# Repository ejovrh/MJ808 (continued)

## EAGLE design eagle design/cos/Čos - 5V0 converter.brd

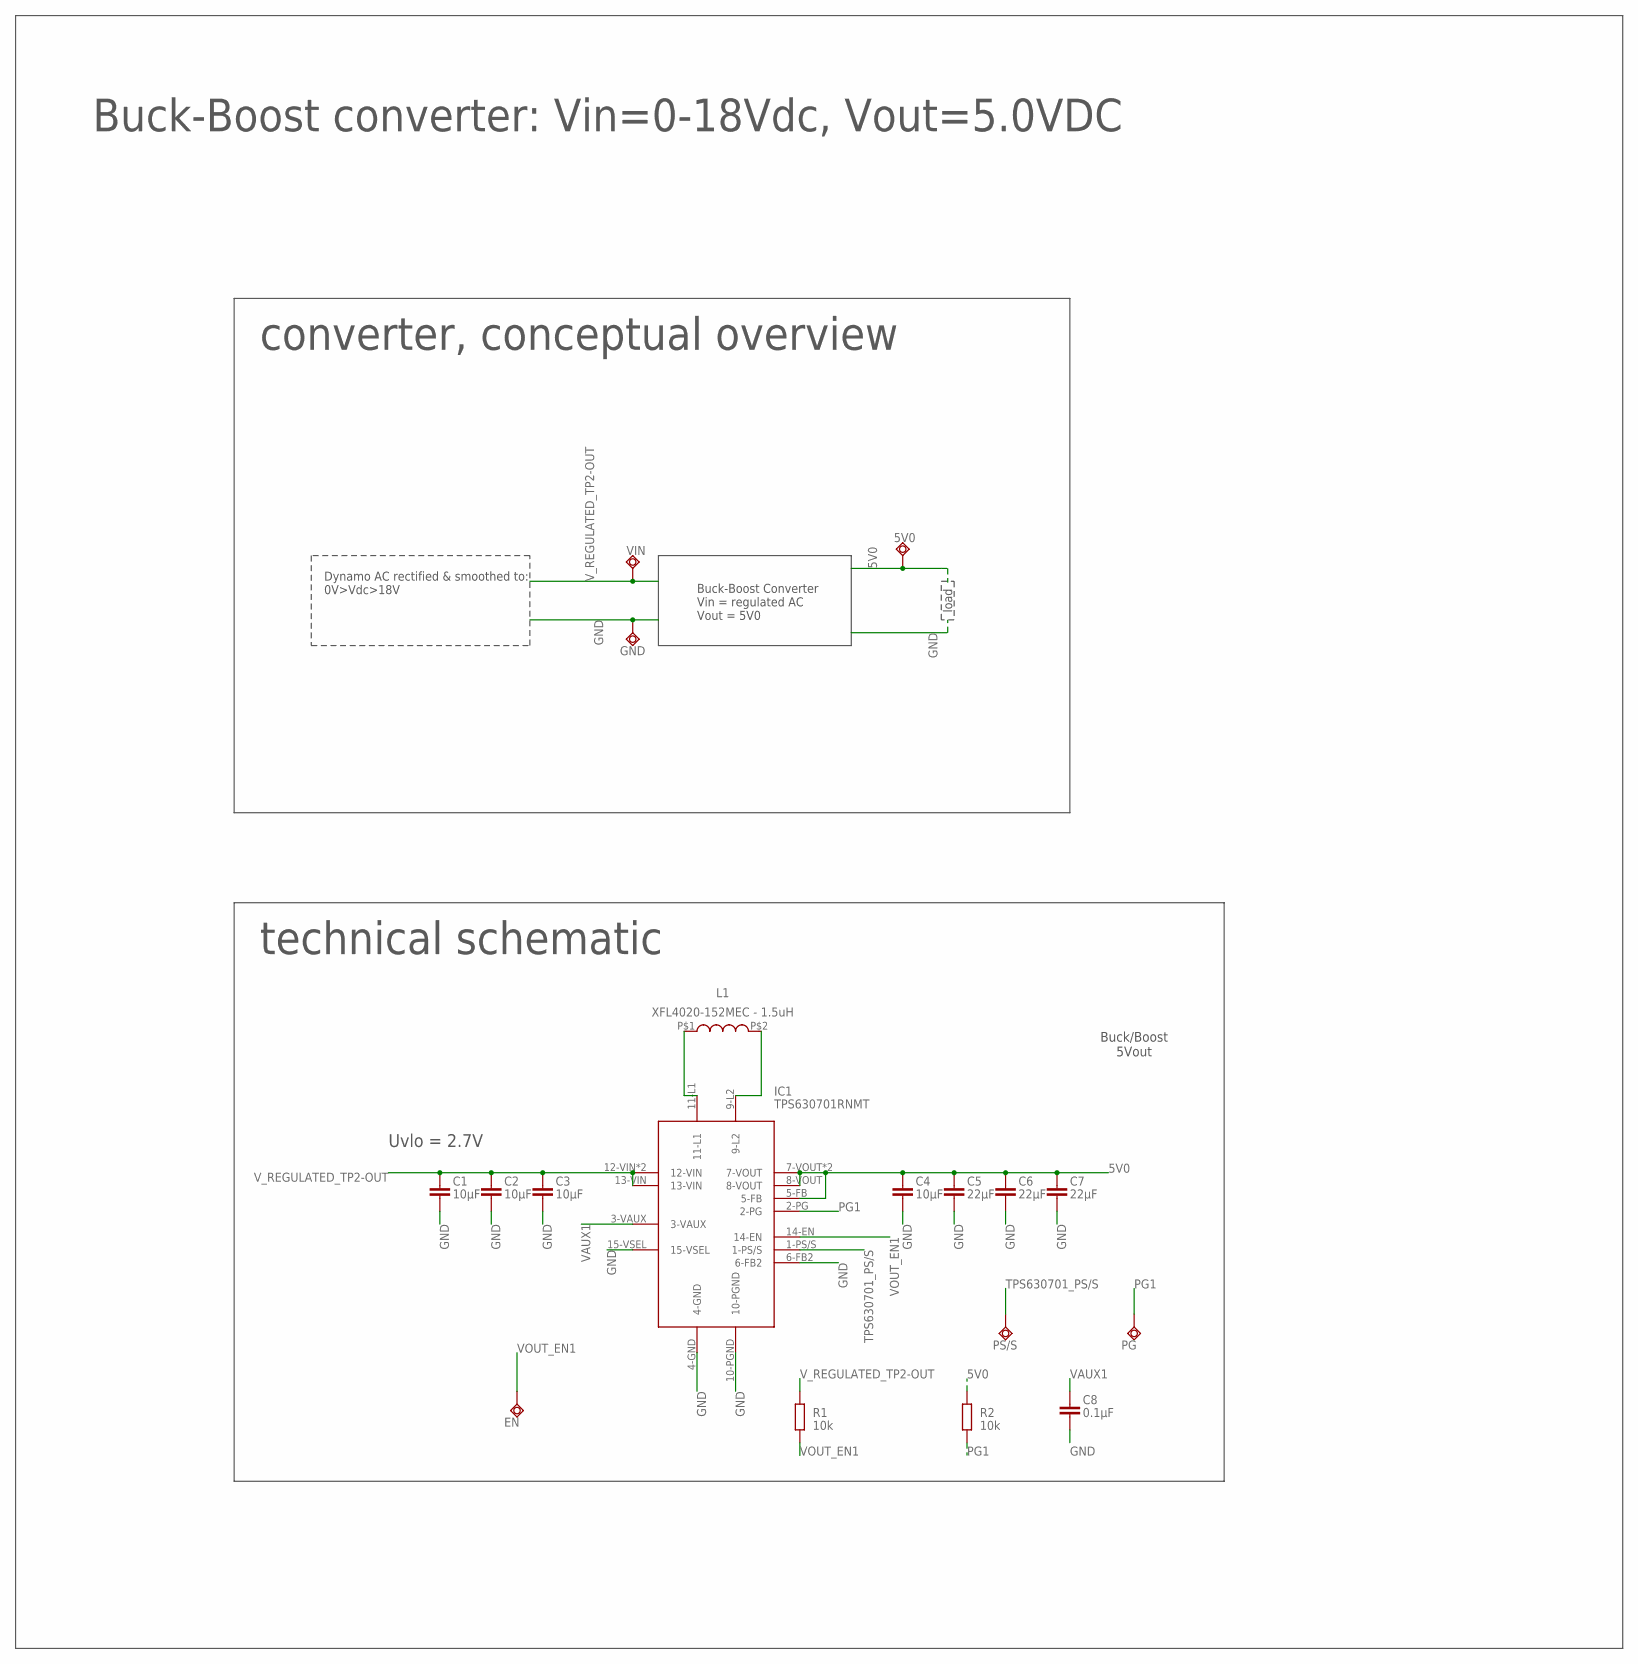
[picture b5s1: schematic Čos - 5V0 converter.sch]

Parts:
5V0: TPSQPAD1-13; P1-13
C1, C2: 10μF; C0805
C3, C4: 10μF; C0603
C5, C6, C7: 22μF; C0805
C8: 0.1μF; C0402
EN: TPSQTP13R; TP13R
GND: TPSQPAD1-13; P1-13
IC1: TPS630701RNMT; VQFN
L1: XFL4020-152MEC - 1.5uH; SMD
PG: TPSQTP13R; TP13R
PS/S: TPSQTP13R; TP13R
R1, R2: 10k; R0402
VIN: TPSQPAD1-13; P1-13

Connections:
5V0: 5V0.TP, C4.1, C5.1, C6.1, C7.1, IC1.5-FB, IC1.7-VOUT, IC1.8-VOUT, IC1.VOUT (7-VOUT), R2.2
GND: C1.2, C2.2, C3.2, C4.2, C5.2, C6.2, C7.2, C8.2, GND.TP, IC1.4-GND, IC1.6-FB2, IC1.10-PGND, IC1.15-VSEL
unnamed: IC1.11-L1, L1.P$1
unnamed: IC1.9-L2, L1.P$2
PG1: IC1.2-PG, PG.TP, R2.1
TPS630701_PS/S: IC1.1-PS/S, PS/S.TP
VAUX1: C8.1, IC1.3-VAUX
VOUT_EN1: EN.TP, IC1.14-EN, R1.1
V_REGULATED_TP2-OUT: C1.1, C2.1, C3.1, IC1.12-VIN, IC1.13-VIN, IC1.VIN (12-VIN), R1.2, VIN.TP

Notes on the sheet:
Buck-Boost converter: Vin=0-18Vdc, Vout=5.0VDC
technical schematic
converter, conceptual overview
Buck/Boost 5Vout
Uvlo = 2.7V
Buck-Boost Converter Vin = regulated AC Vout = 5V0
Dynamo AC rectified & smoothed to: 0V>Vdc>18V
load

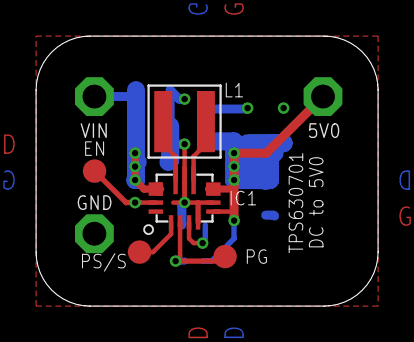
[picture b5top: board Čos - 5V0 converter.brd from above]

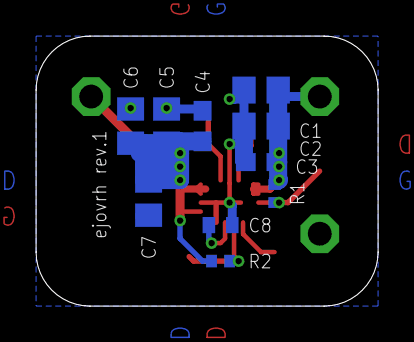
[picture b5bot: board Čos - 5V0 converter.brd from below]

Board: 2 copper layers, 19.0 x 15.0 mm, 18 parts (10 on the bottom side), 9 nets.

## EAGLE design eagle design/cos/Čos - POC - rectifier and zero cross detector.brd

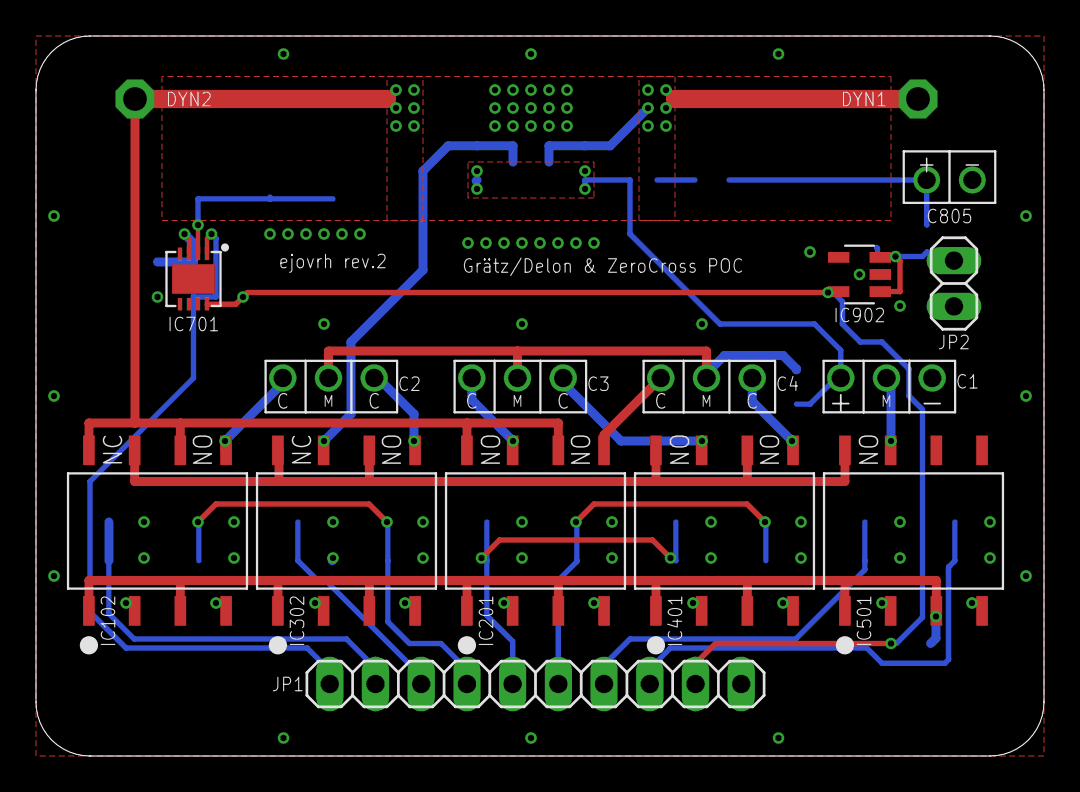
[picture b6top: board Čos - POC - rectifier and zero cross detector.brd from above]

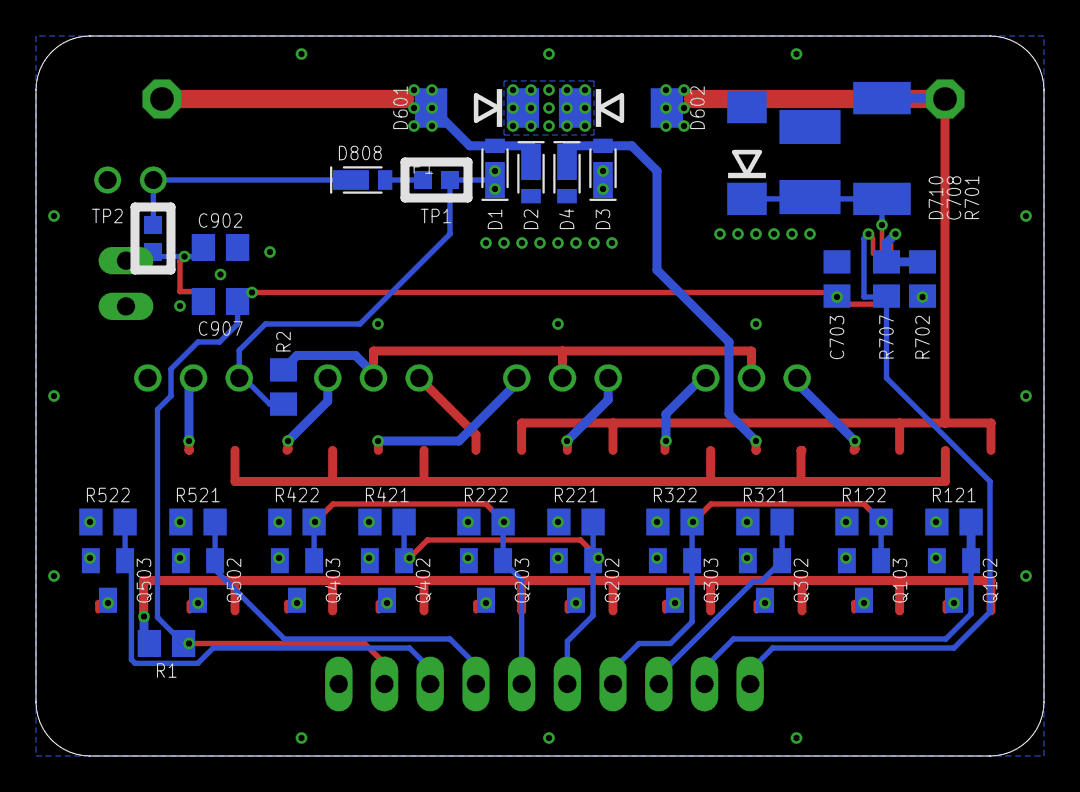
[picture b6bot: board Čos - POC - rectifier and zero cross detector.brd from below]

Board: 2 copper layers, 56.0 x 40.0 mm, 57 parts (41 on the bottom side), 40 nets.

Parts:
C1: 330μF / 35V / ultralow ESR; TH-2S
C2, C3, C4: 1500μF / 35V / ultralow ESR; TH-2S-BACK-TO-BACK
C703: 0.1uF / 10V; C0805
C708: 10nF / 100v; C1812
C805: 2P 4700μF / 35V / ultralow ESR; TH
C902, C907: 1uF / 10V; C0805
D1, D2, D3, D4, D808: CUHS20S30,H3F; US2H
D601, D602: 19V/5W; DO214AA
D710: 6V/3W; DO214AA
IC102, IC302: LBA710S; SMD_DIP8
IC201, IC401, IC501: LAA710S; SMD_DIP8
IC701: LT1638IDD#PBF; DFN-8
IC902: LDK320AM33R; SOT-23-5L
JP1: 2.54-pinhead; 1X10
JP2: 2.54-pinhead; 1X02
Q102, Q103, Q202, Q203, Q302, Q303, Q402, Q403, Q502, Q503: IRLML2402TRPBF; SOT23
R1: 430R/0.5W; R0805
R2: 47k; R0805
R121, R122, R221, R222, R321, R322, R421, R422, R521, R522, R702, R707: 10k; R0805
R701: 10k/3W; R2512
TP2: dynamo 1; P1-13
TP3: dynamo 2; P1-13
TP4: TP1l; TP10SQ
TP5: TP1r; TP10SQ
TP6: TP2l; TP10SQ
TP7: TP2r; TP10SQ

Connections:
+3V3: C703.2, C907.2, IC701.8_V+, IC902.OUT, JP1.9, R1.2
CAA: C2.1_C, IC102.5_DRAIN2-1
CAB: C2.3_C, IC302.5_DRAIN2-1
CBA: C3.1_C, IC201.7_DRAIN1-1
CBB: C3.3_C, IC401.7_DRAIN1-1
CCA: C4.1_C, IC201.5_DRAIN2-1
CCB: C4.3_C, IC401.5_DRAIN2-1
DYNAMO1: D1.C, D2.A, D601.A, TP2.TP
DYNAMO2_AFTER_TUNING-CAP_SW: IC102.7_DRAIN1-1, IC302.6_DRAIN2-2, IC302.8_DRAIN1-2, IC401.6_DRAIN2-2, IC401.8_DRAIN1-2, IC501.8_DRAIN1-2
DYNAMO2_BEFORE_TUNING-CAP_SW: D602.A, IC102.6_DRAIN2-2, IC102.8_DRAIN1-2, IC201.6_DRAIN2-2, IC201.8_DRAIN1-2, R701.1, TP3.TP
DYNAMO2_DELON: C1.2_MID, IC501.7_DRAIN1-1
DYNAMO2_GRAETZ: D3.C, D4.A, IC302.7_DRAIN1-1
GND: C1.3_NEG, C703.1, C708.1, C805.NEG, C902.2, C907.1, D2.C, D4.C, D710.A, IC701.4_V-, IC701.9_V-, IC902.GND, JP1.10, JP2.2, Q102.2, Q103.2, Q202.2, Q203.2, Q302.2, Q303.2, Q402.2, Q403.2, Q502.2, Q503.2, R121.2, R122.2, R221.2, R222.2, R321.2, R322.2, R421.2, R422.2, R521.2, R522.2, R702.1
unnamed: JP1.8, Q503.1, R522.1
OVP:ZENER_COMMON: D601.C, D602.C
SSR_ANODE: IC102.1_ANODE1, IC102.3_ANODE2, IC201.1_ANODE1, IC201.3_ANODE2, IC302.1_ANODE1, IC302.3_ANODE2, IC401.1_ANODE1, IC401.3_ANODE2, IC501.1_ANODE1, IC501.3_ANODE2, R1.1
SSR_NC/NO1:SW1_CAT: IC102.2_CATHODE1, Q102.3
SSR_NC/NO1:SW2_CAT: IC102.4_CATHODE2, Q103.3
SSR_NC/NO2:SW1_CAT: IC302.2_CATHODE1, Q302.3
SSR_NC/NO2:SW2_CAT: IC302.4_CATHODE2, Q303.3
SSR_NO/NO1:SW1_CAT: IC201.2_CATHODE1, Q202.3
SSR_NO/NO1:SW2_CAT: IC201.4_CATHODE2, Q203.3
SSR_NO/NO2:SW1_CAT: IC401.2_CATHODE1, Q402.3
SSR_NO/NO2:SW2_CAT: IC401.4_CATHODE2, Q403.3
SSR_NO/NO3:SW1_CAT: IC501.2_CATHODE1, Q502.3
SSR_NO/NO3:SW2_CAT: IC501.4_CATHODE2, Q503.3
SW1_CTRL: JP1.2, Q102.1, R121.1
SW2_CTRL: JP1.3, Q302.1, R321.1
SW9_CTRL: JP1.7, Q502.1, R521.1
SW_CA_CTRL: JP1.4, Q103.1, Q303.1, R122.1, R322.1
SW_CB_CTRL: JP1.5, Q202.1, Q402.1, R221.1, R421.1
SW_CC_CTRL: JP1.6, Q203.1, Q403.1, R222.1, R422.1
TUNING_CAP_BIAS: C2.2_MID, C3.2_MID, C4.2_MID, R2.1
V_RECT_TP1-IN: C1.1_POS, D1.A, D3.A, R2.2, TP4.TP
V_RECT_TP1-OUT: D808.C, TP5.TP
V_REGULATED_TP2-IN: C805.POS, D808.A, TP6.TP
V_REGULATED_TP2-OUT: C902.1, IC902.EN, IC902.IN, JP2.1, TP7.TP
ZERO-CROSS_DETECTOR:N$6: C708.2, D710.C, IC701.2_A_IN-, R701.2
ZERO-CROSS_DETECTOR:N$12: IC701.3_A_IN+, R702.2, R707.2
ZEROCROSS: IC701.1_A_OUT, JP1.1, R707.1

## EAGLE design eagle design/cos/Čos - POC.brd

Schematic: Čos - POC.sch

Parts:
C1, C2, C27, C28: 10μF; C0805
C3, C5, C29, C30: 10μF; C0603
C4: 1μF; C0402
C6, C9: 10pF; C0402
C7, C10, C11, C17, C21, C22, C25, C26, C34: 0.1μF; C0402
C8, C24: 4.7μF; C0402
C12, C15, C16, C31, C32, C33: 22μF; C0805
C13, C14: 330μF / 35V / ultralow ESR; TH
C18, C19: 3300μF / 35V / ultralow ESR; TH
C20: 10μF; C0402
C23: 4700μF / 35V / ultralow ESR; TH
D1, D2: SMBJ5356B-TP; DO214AA
D3, D4, D5, D6, D7, D8, D9: CUHS20S30,H3F; US2H
FD1, FD2, FD3: FID_40MIL; FID_040
H: CAN High; SMT-1.2MM
IC1: LT1001CS8#PBF; SO08
IC2, IC8: LBA710S; SMD_DIP6
IC3: TPS630701RNMT; VQFN
IC4: LMP92064SD/NOPB; WSON-16
IC5: ATTINY4313-MMH; VQFN-20
IC6: AWSCR-8.00CELA-C10-T3; SMT
IC7: MCP73871-1CCI/ML; QFN50P400X400X100-21N
IC9: MCP2515; QFN20
IC10: MCP23S08-E/ML; QFN20
IC11: AD5160BRJZ5-R2; SOT-23-8
IC12: MCP2561-2; DFN10
IC13: TPS63070RNMR; VQFN
ICSP: 5034800600; SMT
L: CAN Low; SMT-1.2MM
L1, L2: XFL4020-152MEC - 1.5uH; SMD
LI-ION: 505567-0371; SMT
N1, N2: Li-Ion Cell +; P1-13
R1: 43mR, 200mW; R2512
R2, R11, R18, R21, R25: 100k; R0402
R3, R9, R12, R17, R26: 10k; R0402
R4: 270k; R0402
R5: 110k; R0402
R6, R7, R8, R19: 47k; R0402
R10: 324k; R0402
R13: 1k; R0402
R14: 150k; R0402
R15: 741X083331JP / 330Ω; 0402-4R
R16: 741X083103JP / 10kΩ; 0402-4R
R20: 400k; R0402
R22: 741X083221JP / 220Ω; 0402-4R
R23: 680k; R0402
R24: 130k; R0402
TP1, TP2, TP5, TP6, TP7, TP8, TP9, TP10, TP11, TP12, TP13, TP14: PTR1TP10SQ; TP10SQ

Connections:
5V0_TP-IN: C5.1, C12.1, C15.1, C16.1, IC3.5-FB, IC3.7-VOUT, IC3.8-VOUT, IC3.VOUT (7-VOUT), R18.2, TP7.TP
5V0_TP-OUT: C6.1, C7.1, C9.1, C10.1, C11.1, C20.1, C21.1, C22.1, C25.1, C26.1, IC1.7 (V+), IC4.8_VDD (VDD_8), IC4.9_VDIG (VDIG_9), IC5.18 (VCC), IC7.3_SEL (SEL), IC7.4_PROG2 (PROG2), IC7.9_!TE! (!TE!), IC7.18_IN1 (IN), IC7.19_IN2 (IN), IC9.VDD, IC10.4_!RESET!, IC10.18_VCC, IC11.2_VDD (VDD_2), IC12.VDD (VCC), ICSP.5, R2.1, R4.2, R6.2, R7.2, R8.2, R10.2, R15.8, R16.1, R16.3, R16.5, R16.7, R17.2, R20.1, TP8.TP
ANODE_DELON: IC8.3_ANODE2, R22.2
ANODE_GRAETZ: IC8.1_ANODE1, R22.4
ANODE_TUNING-CAP: IC2.3_ANODE2, R22.6
ANODE_TUNING-CAP_BYPASS: IC2.1_ANODE1, R22.8
CANH: H.P$1, IC12.CANH
CANL: IC12.CANL, L.P$1
CLOCKOUT: IC5.4 (PCINT13/CKOUT/XCK/INT0-PD2), IC9.OSC1
COMPARATOR_IN: IC1.6 (OUT), IC5.10 (AIN0/PCINT0-PB0)
COMPARATOR_REF: IC5.11 (AIN1/PCINT1-PB1), R20.2, R21.1
DEBUGWIRE/RESET: IC5.19 (!RESET!/DW/PCINT10-PA2), ICSP.6
DELON-NO: IC10.13_GP4, R22.1
DYNAMO1: D1.A, D3.C, D4.A, IC1.3 (+IN), N1.TP
DYNAMO2_AFTER_TUNING-CAP_SW: C18.NEG, IC2.5_DRAIN2-1
DYNAMO2_BEFORE_G/D: C19.NEG, IC2.7_DRAIN1-1, IC8.6_DRAIN2-2, IC8.8_DRAIN1-2
DYNAMO2_BEFORE_TUNING-CAP_SW: D2.A, IC2.6_DRAIN2-2, IC2.8_DRAIN1-2, N2.TP
DYNAMO2_DELON: C13.NEG, C14.POS, IC8.5_DRAIN2-1
DYNAMO2_GRAETZ: D5.C, D6.A, IC8.7_DRAIN1-1
FB2: IC13.5-FB, R23.1, R24.2
GND_VIA_INCP: C1.2, C2.2, C3.2, C4.2, C5.2, C6.2, C7.2, C8.2, C9.2, C10.2, C11.2, C12.2, C15.2, C16.2, C17.2, C20.2, C21.2, C22.2, C24.1, C25.2, C26.2, C27.2, C28.2, C29.2, C30.2, C31.2, C32.2, C33.2, C34.2, IC1.4 (V-), IC2.2_CATHODE1, IC2.4_CATHODE2, IC3.4-GND, IC3.6-FB2, IC3.10-PGND, IC3.15-VSEL, IC4.2_REFG, IC4.3_INCP, IC4.6_INVG, IC4.7_GND, IC4.10_DGND, IC4.16_RESET (RESET_16), IC4.GND1 (7_GND), IC5.8 (GND), IC5.GND, IC6.GND, IC7.10_GND1 (GND), IC7.11_GND2 (GND), IC7.GND2 (GND), IC7.GND3 (GND), IC7.GND4 (GND), IC7.GND5 (GND), IC7.GND6 (GND), IC8.2_CATHODE1, IC8.4_CATHODE2, IC9.GND, IC9.GND6 (GND), IC10.2_A1, IC10.3_A0, IC10.17_GND (GND), IC10.GND, IC11.3_GND, IC11.7_B (B_7), IC12.GND, IC12.VSS (GND), IC13.4-GND, IC13.6-FB2, IC13.10-PGND, IC13.15-VSEL, ICSP.1, ICSP.GND1 (GND), ICSP.GND2 (GND), LI-ION.GND1 (GND), LI-ION.GND2 (GND), LI-ION.P$3, R1.2, R5.1, R9.1, R14.1, R21.2, R24.1, R26.1
GRAETZ_NC: IC10.14_GP5, R22.3
HH: C14.NEG, C23.NEG, D4.C, D6.C, R3.1, R11.1, TP2.TP
ICSP_DI/MISO: IC5.15 (MOSI/DI/SDA/PCINT5-PB5), ICSP.2, R15.5
ICSP_DO/MOSI: IC5.16 (MISO/DO/PCINT6-PB6), ICSP.3, R15.3
ICSP_SCK: IC5.17 (USCK/SCL/SCK/PCINT7-PB7), ICSP.4, R15.1
INCN: IC4.4_INCN, R1.1, TP1.TP
INT_MCP23S08: IC5.6 (PCINT15/T0-PD4), IC10.7_INT
INT_MCP2515: IC5.5 (PCINT14/INT1-PD3), IC9.!INT!
INVP: IC4.5_INVP, R10.1, R11.2
MCP73871_CE: IC7.17_CE (CE), IC10.12_GP3
MCP73871_PG_PIN: IC7.!6_PG! (!PG!), IC10.11_GP2, R6.1
MCP73871_STAT1/!LBO!_PIN: IC7.8_STAT1/!LBO! (STAT1/!LBO!), IC10.9_GP0, R7.1
MCP73871_STAT2_PIN: IC7.7_STAT2 (STAT2), IC10.10_GP1, R8.1
unnamed: IC3.11-L1, L1.P$1
unnamed: IC3.9-L2, L1.P$2
unnamed: IC13.11-L1, L2.P$1
unnamed: IC13.9-L2, L2.P$2
unnamed: C4.1, IC4.1_REFC (REFC_1)
NTC: LI-ION.P$2, R13.2, R14.2
OPAMP_NEG: IC1.2 (-IN), R2.2, R3.2
PG1: IC3.2-PG, R18.1
PG2: IC13.2-PG, R25.1
PROG1: IC7.13_PROG1 (PROG1), IC11.1_W (W_1)
PROG3: IC7.12_PROG3 (PROG3), R9.2
RESET: IC9.!RESET!, R16.4
RXCAN: IC9.RXCAN, IC12.RXD
SOLAR-CELL_TP-IN: TP14.TP
SOLAR-CELL_TP-OUT: D9.C, TP13.TP
SPI_MISO: IC4.11_SDO (SDO_11), IC9.SO, IC10.1_MISO, R15.6
SPI_MOSI: IC4.12_SDI (SDI_12), IC9.SI, IC10.20_MOSI, IC11.5_SDI, R15.4
SPI_SCK: IC4.13_SCLK (SCLK_13), IC9.SCK, IC10.19_SCK, IC11.4_CLK, R15.2
SPI_SS_AD5160: IC5.7 (PCINT16/OC0B/T1-PD5), IC11.6_!CS!, R16.8
SPI_SS_LMP92064SD: IC4.14_CSB (CSB_14), IC5.9 (PCINT17/ICPI-PD6), R16.6
SPI_SS_MCP23S08: IC5.1 (PCINT12/TXD-PD1), IC10.5_!CS!, R17.1
SPI_SS_MCP2515: IC5.14 (OC1B/PCINT4-PB4), IC9.!CS!, R15.7
STBY: IC5.13 (OC1A/PCINT3-PB3), IC12.STBY, R16.2
THERM: IC7.5_THERM (THERM), R13.1
TPS630701_PWM: IC3.1-PS/S, IC5.12 (OC0A/PCINT2-PB2), IC13.1-PS/S
TUNING-CAP_BYPASS_NC: IC10.16_GP7, R22.7
TUNING-CAP_NO: IC10.15_GP6, R22.5
TUNIN_CAP_BIAS: C18.POS, C19.POS, R19.1
TXCAN: IC9.TXCAN, IC12.TXD
VAUX1: C17.1, IC3.3-VAUX
VAUX2: C34.1, IC13.3-VAUX
VOUT: C30.1, C31.1, C32.1, C33.1, IC13.7-VOUT, IC13.8-VOUT, IC13.VOUT (7-VOUT), R23.2
VOUT_EN1: IC3.14-EN, R12.1
VOUT_EN2: IC5.20 (RXD/PCINT11-PD0), IC13.14-EN, R26.2
VPCC: IC7.2_VPCC (VPCC), R4.1, R5.2
V_LI-ION_BATTERY-CELL: C8.1, IC7.14_VBAT1 (VBAT), IC7.15_VBAT2 (VBAT), IC7.16_BAT_SENSE (VBAT_SENSE), LI-ION.P$1
V_LI-ION_OUT: C24.2, C27.1, C28.1, C29.1, IC7.1_OUT1 (OUT), IC7.20_OUT2 (OUT), IC13.12-VIN, IC13.13-VIN, IC13.VIN (12-VIN), R25.2, TP11.TP
V_LI-ION_TP-OUT: D8.C, TP12.TP
V_RECT_TP-IN: C13.POS, D3.A, D5.A, R19.2, TP5.TP
V_RECT_TP-OUT: D7.C, TP6.TP
V_REGULATED_TP-IN: C23.POS, D7.A, TP9.TP
V_REGULATED_TP-OUT: C1.1, C2.1, C3.1, D8.A, D9.A, IC3.12-VIN, IC3.13-VIN, IC3.VIN (12-VIN), R12.2, TP10.TP
XTAL1: IC5.3 (PCINT8/CLKI/XTAL1-PA0), IC6.XTAL1
XTAL2: IC5.2 (PCINT9/XTAL2-PA1), IC6.XTAL2
ZENER_COMMON: D1.C, D2.C

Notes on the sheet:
P.18, 3.6
p.23, 4.5 Constant Current Mode - Fast Charge, 5.1.2 Ireg = 1000v/Rprog1 500mA = 1000V/2000Ω
p.23, 4.7 Charge Termination Iterm = 1000V/Rprog3 100mA=1000V/10kΩ
p.17, Voltage Proportional Charge Control Vpcc=(R2/(R1+R2))*Vin
P.18, 3.4
P.18, 3.9
Vzener = 19V
Tuning Capacitor Bank
Delon Voltage Doubler
graetz bridge
V_dc
Vac
Graetz Bridge Rectifier consists of 4 ideal diodes & ideal diode controller D1-4 - ideal diodes
tuning cap.
Dynamo Connector & Overvoltage Protection Diodes
smoothing cap
LOAD
Graetz Rectifier
Delon voltage doubler
relay
TP1
TP2
AC Rectifier
Load
rectified and Smoothed Voltage to 5V0 Buck-Boost Converter
Buck-Boost Converter Vin = regulated AC Vout = 5V0
5V0
GND
Dynamo AC regulated output
Li-Ion Battery Powerpath Charger
Li-Ion Battery
4V2
0V> Vdc > 18V
DC Boost converter 6V0 out
TODO - consolidate SPI SS pullups
graetz
tuning cap
delon
TP4
ideal diode

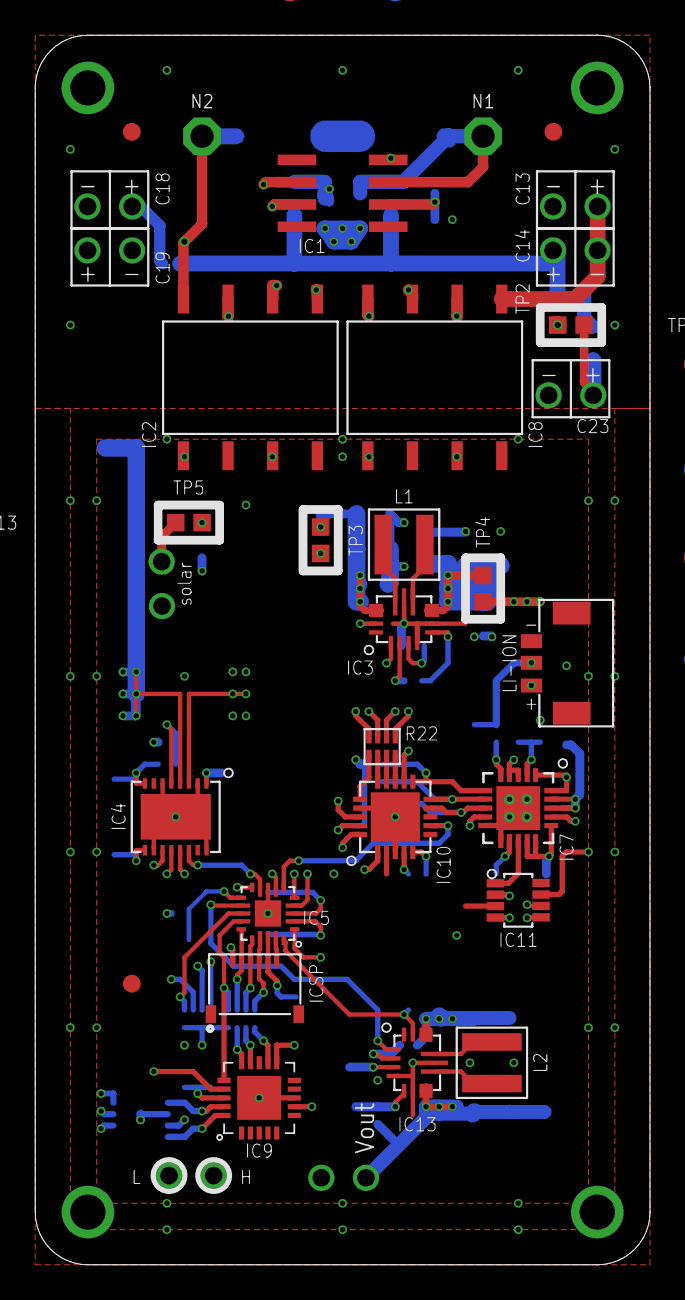
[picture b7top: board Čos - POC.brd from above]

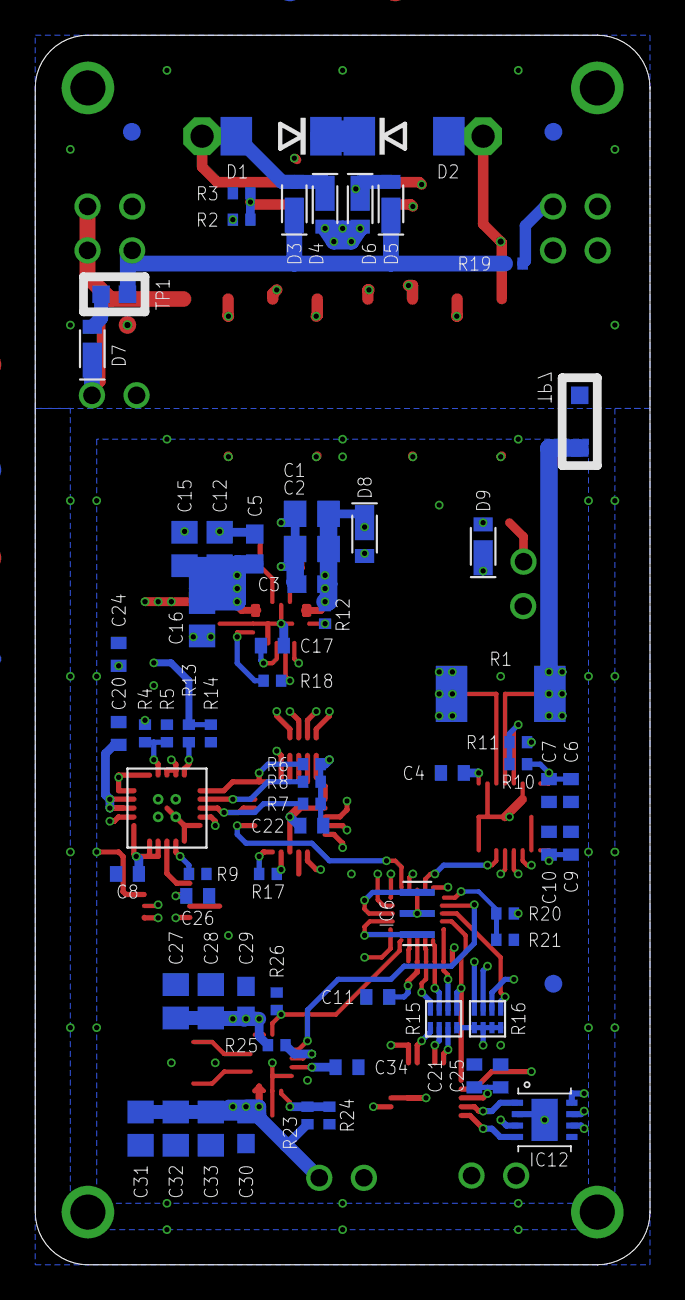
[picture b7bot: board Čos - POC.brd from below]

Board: 4 copper layers, 35.0 x 70.0 mm, 105 parts (70 on the bottom side), 78 nets.

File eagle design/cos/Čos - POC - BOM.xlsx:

Qty | Value | Device | Package | Parts | mouser part no. | mouser url
1 | 5034800600 | 5034800600 | SMT | ICSP | 538-503480-0600 | https://hr.mouser.com/ProductDetail/?qs=bodV9ulq6Gw510ukaFX%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
9 | 0.1μF | C-EUC0402 | C0402 | C7, C10, C11, C17, C21, C22, C25, C26, C34 | 80-C0402C104K4R | https://hr.mouser.com/ProductDetail/KEMET/C0402C104K4RACTU?q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
5 | 100k | R-EU_R0402 | R0402 | R2, R11, R18, R21, R25 | 71-RCS0402100KFKED | https://hr.mouser.com/ProductDetail/Vishay-Dale/RCS0402100KF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
5 | 10k | R-EU_R0402 | R0402 | R3, R9, R12, R17, R26 | 71-RCS040210K0FKED | https://hr.mouser.com/ProductDetail/Vishay-Dale/RCS040210K0F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
2 | 10pF | C-EUC0402 | C0402 | C6, C9 | 80-C0402C100K4RAUTO | https://hr.mouser.com/ProductDetail/KEMET/C0402C100K4RACAUTO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
1 | 10μF | C-EUC0402 | C0402 | C20 | 80-C0402C106M9P | https://hr.mouser.com/ProductDetail/KEMET/C0402C106M9PACTU?q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
4 | 10μF | C-EUC0603 | C0603 | C3, C5, C29, C30 | 80-C0603C106M8PACTU | https://hr.mouser.com/ProductDetail/KEMET/C0603C106M8PACTU?q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
4 | 10μF | C-EUC0805 | C0805 | C1, C2, C27, C28 | 80-C0805C106K3P | https://hr.mouser.com/ProductDetail/KEMET/C0805C106K3PACTU?q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
1 | 110k | R-EU_R0402 | R0402 | R5 | 71-CRCW0402-110-E3 | https://hr.mouser.com/ProductDetail/Vishay-Dale/CRCW0402110R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
1 | 130k | R-EU_R0402 | R0402 | R24 | 71-CRCW0402-130K-E3 | https://hr.mouser.com/ProductDetail/Vishay-Dale/CRCW0402130K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
1 | 150k | R-EU_R0402 | R0402 | R14 | 71-RCS0402150KFKED | https://hr.mouser.com/ProductDetail/Vishay-Dale/RCS0402150KF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
1 | 1k | R-EU_R0402 | R0402 | R13 | 71-RCS04021K00FKED | https://hr.mouser.com/ProductDetail/Vishay-Dale/RCS04021K00F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
1 | 1μF | C-EUC0402 | C0402 | C4 | 80-C0402C105K4P | https://hr.mouser.com/ProductDetail/KEMET/C0402C105K4PACTU?q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
6 | 22μF | C-EUC0805 | C0805 | C12, C15, C16, C31, C32, C33 | 80-C0805C226M8P | https://hr.mouser.com/ProductDetail/KEMET/C0805C226M8PACTU?q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
1 | 270k | R-EU_R0402 | R0402 | R4 | 71-CRCW0402270KFKED | https://hr.mouser.com/ProductDetail/Vishay-Dale/CRCW0402270K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
1 | 324k | R-EU_R0402 | R0402 | R10 | 71-CRCW0402-324K-E3 | https://hr.mouser.com/ProductDetail/Vishay-Dale/CRCW0402324K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
2 | 3300μF / 35V / ultralow ESR | C-POL | TH | C18, C19 | 647-UHE1V332MHD6 | https://hr.mouser.com/ProductDetail/647-UHE1V332MHD6
2 | 330μF / 35V / ultralow ESR | C-POL | TH | C13, C14 | 647-UHD1V331MPD | https://hr.mouser.com/ProductDetail/647-UHD1V331MPD
2 | 4.7μF | C-EUC0402 | C0402 | C8, C24 | 80-C0402C475M9P | https://hr.mouser.com/ProductDetail/KEMET/C0402C475M9PACTU?q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
1 | 400k | R-EU_R0402 | R0402 | R20 | 71-CRCW0402402KFKEDC | https://hr.mouser.com/ProductDetail/Vishay-Dale/CRCW0402402K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
1 | 43mR, 200mW | R-EU_R2512 | R2512 | R1 | 660-SLW1TTE43L0D | https://hr.mouser.com/ProductDetail/KOA-Speer/SLW1TTE43L0D?q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
1 | 4700μF / 35V / ultralow ESR | C-POL | TH | C23 | 647-UPW1V472MHD | https://hr.mouser.com/ProductDetail/647-UPW1V472MHD
4 | 47k | R-EU_R0402 | R0402 | R6, R7, R8, R19 | 71-RCS040247K0FKED | https://hr.mouser.com/ProductDetail/Vishay-Dale/RCS040247K0F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
1 | 505567-0371 | 505567 | SMT | LI-ION | 538-505567-0371 | https://hr.mouser.com/ProductDetail/Molex/505567-0371?qs=sGA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
1 | 680k | R-EU_R0402 | R0402 | R23 | 71-CRCW0402680KFKED | https://hr.mouser.com/ProductDetail/Vishay-Dale/CRCW0402680K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
1 | 741X083103JP / 10kÎ© | 741X083331JP | 0402-4R | R16 | 774-741X083103JP | https://hr.mouser.com/ProductDetail/CTS-Electronic-Component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
1 | 741X083221JP / 220Î© | 741X083331JP | 0402-4R | R22 | 774-741X083221JP | https://hr.mouser.com/ProductDetail/CTS-Electronic-Component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
1 | 741X083331JP / 330Î© | 741X083331JP | 0402-4R | R15 | 774-741X083331JP | https://hr.mouser.com/ProductDetail/CTS-Electronic-Component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
1 | AD5160BRJZ5-R2 | AD5160 | SOT-23-8 | IC11 | 584-AD5160BRJZ5-R7 | https://hr.mouser.com/ProductDetail/Analog-Devices/AD5160BRJ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
1 | ATTINY4313-MMH | ATTINY4313VQFN-20 | VQFN-20 | IC5 | 556-ATTINY4313-MMH | https://hr.mouser.com/ProductDetail/Microchip-Technology-Atm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
1 | AWSCR-8.00CELA-C10-T3 | PRQV | SMT | IC6 | 815-CR-8.00CELA-10-T | https://hr.mouser.com/ProductDetail/?qs=T3oQrply3y9BQA7AUwI%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
7 | CUHS20S30,H3F | CUHS20S30 | US2H | D3, D4, D5, D6, D7, D8, D9 | 757-CUHS20S30H3F | https://hr.mouser.com/ProductDetail/Toshiba/CUHS20S30H3F?qs=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
2 | LBA710S | LBA710 | SMD_DIP6 | IC2, IC8 | 849-LBA710S | https://hr.mouser.com/ProductDetail/IXYS-Integrated-Circuits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
1 | LMP92064SD/NOPB | LMP92064SD | WSON-16 | IC4 | 595-LMP92064SD/NOPB | https://hr.mouser.com/ProductDetail/Texas-Instruments/LMP920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
1 | LT1001CS8#PBF | LT1007CS8 | SO08 | IC1 | 584-LT1001CS8#PBF | https://hr.mouser.com/ProductDetail/Analog-Devices-Linear-Te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
1 | MCP23S08-E/ML | MCP23S08 | QFN20 | IC10 | 579-MCP23S08T-E/ML | https://hr.mouser.com/ProductDetail/Microchip-Technology/MCP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
1 | MCP2515 | MCP2515-I-ML | QFN20 | IC9 | 579-MCP2515-I/ML | https://hr.mouser.com/ProductDetail/?qs=98WN%2FnWUQiTu5rc2r0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
1 | MCP2561-2 | MCP2561-2 | DFN10 | IC12 | 579-MCP2561T-E/MF | https://hr.mouser.com/ProductDetail/?qs=6qKXPk0vzx33CQz7j2oI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
1 | MCP73871-1CCI/ML | MCP73871-2AAI/ML | QFN50P400X400X100-21N | IC7 | 579-MCP73871-1CCI/ML | https://hr.mouser.com/ProductDetail/Microchip-Technology/MCP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
2 | SMBJ5356B-TP | DIODE-DO214AA | DO214AA | D1, D2 | 833-SMBJ5356B-TP | https://hr.mouser.com/ProductDetail/Micro-Commercial-Compone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
1 | TPS630701RNMT | TPS630701 | VQFN | IC3 | 595-TPS630701RNMR | https://hr.mouser.com/ProductDetail/Texas-Instruments/TPS630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
1 | TPS63070RNMR | TPS630701 | VQFN | IC13 | 595-TPS63070RNMR | https://hr.mouser.com/ProductDetail/Texas-Instruments/TPS630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
2 | XFL4020-152MEC - 1.5uH | XFL4020-152MEC | SMD | L1, L2 | 994-XFL4020-152MEC | https://hr.mouser.com/ProductDetail/Coilcraft/XFL4020-152MEC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
10 | crimp contacts |  |  |  | 538-505431-1100 | https://hr.mouser.com/ProductDetail/538-505431-1100
1 | connector for li-ion battery |  |  |  | 538-505565-0301 | https://hr.mouser.com/ProductDetail/538-505565-0301

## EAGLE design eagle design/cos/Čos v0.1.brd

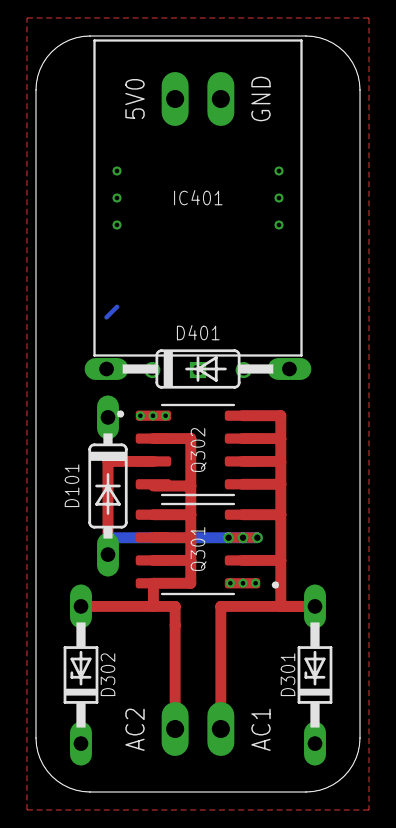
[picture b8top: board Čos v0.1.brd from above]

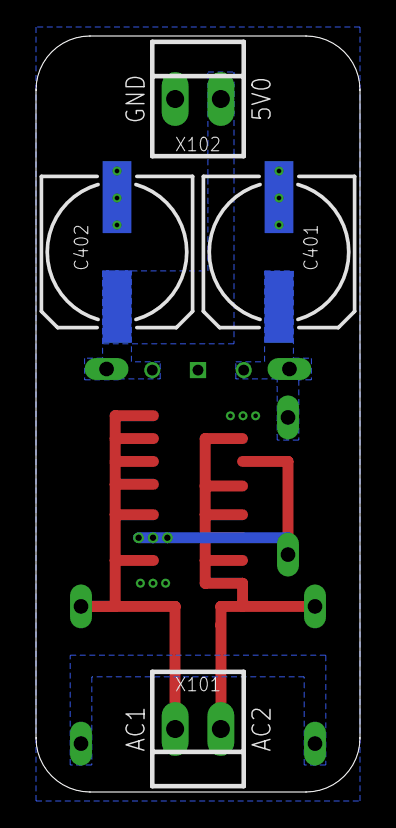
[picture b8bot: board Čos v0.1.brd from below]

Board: 2 copper layers, 18.0 x 42.0 mm, 11 parts (4 on the bottom side), 7 nets.

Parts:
C401: 470u; 153CLV-0807
C402: 22u; 153CLV-0807
D101: 1N4148DO35-7; DO35-7
D301, D302: 1N5362B; DO34Z7
D401: 1N4148DO35-10; DO35-10
IC401: R-78B5.0-1.0L; TH
Q301, Q302: IRF7319; SOIC127P600X175-8N
X101, X102: 22-23-2021

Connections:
5V0: C402.+, D401.A, IC401.OUT, X102.2
AC1: D301.A, Q301.2, Q301.4, Q302.5, Q302.6, Q302.7, Q302.8, X101.2
AC2: D302.A, Q301.5, Q301.6, Q301.7, Q301.8, Q302.2, Q302.4, X101.1
GND: C401.-, C402.-, IC401.GND, Q301.1, Q302.1, X102.1
MOSFET-GRÄTZ:AC_COMMON: D301.C, D302.C
VIN: C401.+, D101.C, D401.C, IC401.IN
VRECT: D101.A, Q301.3, Q302.3
